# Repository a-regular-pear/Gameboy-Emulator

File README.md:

# Gameboy Emulator

A Gameboy emulator for the Teensy 4.1 microcontroller and PC (Windows and Linux).

## Features

* Nearly complete LR35902 (Gameboy CPU) implementation.
* Support for Memory Bank Controllers: MBC0, MBC1, MBC3, and MBC5.
* Native support for Teensy 4.1, Windows, and Linux.
* Runs on the Teensy 4.1 using internal memory (does not require external PSRAM to work).
* APU supports Channel 1 and Channel 2 on PC

## TODO

* Add audio (APU) support.
* Make the PPU (Picture Processing Unit) modes dynamic.
* Add support for the remaining memory banks (e.g., MBC2).
* Design a custom PCB for the Teensy 4.1 hardware setup.

## Software Needed

### For Teensy 4.1

* [PlatformIO](https://platformio.org/)
* [ILI9341_t3n](https://github.com/KurtE/ILI9341_t3n) (Hardware-optimized display library)

### For PC

* A C++17 compatible compiler (GCC)
* [CMake](https://cmake.org/)
* [SDL2](https://www.libsdl.org/) and SDL2_ttf
* For Windows: [MSYS2](https://www.msys2.org/) (UCRT64 environment)

## Build Instructions

### Teensy 4.1

Make sure the hardware pins for the buttons are connected as follows:

* **Right:** 0, **Left:** 1, **Up:** 2, **Down:** 3, **B:** 4, **A:** 5, **Select:** 6, **Start:** 7

Connect the ILI9341 display to the following SPI pins:

* **CS:** 10, **DC:** 9, **RST:** 8, **MOSI:** 11, **SCK:** 13, **MISO:** 12

To build:

1. Open the project in PlatformIO.
2. Make sure you are using the `teensy41` project environment.
3. Compile and upload to the board.
4. To add ROMs, format a MicroSD card (FAT32), load the `.gb` files onto the root directory, and insert it into the Teensy.

### Linux

Install `cmake`, `gcc`, `g++`, and the SDL2 development libraries using your distribution's package manager (e.g., `sudo apt install cmake gcc g++ libsdl2-dev libsdl2-ttf-dev` on Debian/Ubuntu).

Then, navigate to the project directory and run:

```bash
mkdir -p build
cd build
cmake ..
make
./emulator

```

To load ROMs, place the `.gb` files in the same directory as the executable.

### Windows (MSYS2)

**1. Install MSYS2**
Download the installer from [msys2.org](https://www.msys2.org/) and run it. Accept the default installation folder (usually `C:\msys64`). Once finished, open the **MSYS2 UCRT64** terminal (this is the recommended environment for modern Windows development).

**2. Update the System**
In the UCRT64 terminal, update the package database and core system packages:

```bash
pacman -Syu

```

**3. Install the Toolchain and Libraries**
Install the GCC compiler, CMake, standard Make tool, SDL2, and SDL2_ttf using the `pacman` package manager.

*(Note: We are explicitly installing `mingw-w64-ucrt-x86_64-make` instead of Ninja).*

```bash
pacman -S mingw-w64-ucrt-x86_64-gcc \
          mingw-w64-ucrt-x86_64-cmake \
          mingw-w64-ucrt-x86_64-make \
          mingw-w64-ucrt-x86_64-SDL2 \
          mingw-w64-ucrt-x86_64-SDL2_ttf

```

**4. Configure and Build**
Open the **MSYS2 UCRT64** terminal (or standard CMD/PowerShell if you have added MSYS2 to your PATH), navigate to your project folder using the `cd` command, and run the following commands:

**Generate the build files (using MinGW Makefiles):**

```bash
cmake -G "MinGW Makefiles" -B build

```

**Compile the executable:**

```bash
cmake --build build

```

**Run the compiled application:**

```bash
./build/emulator.exe

```

To load ROMs, place the `.gb` files in the directory where `./build/emulator.exe` is executed.

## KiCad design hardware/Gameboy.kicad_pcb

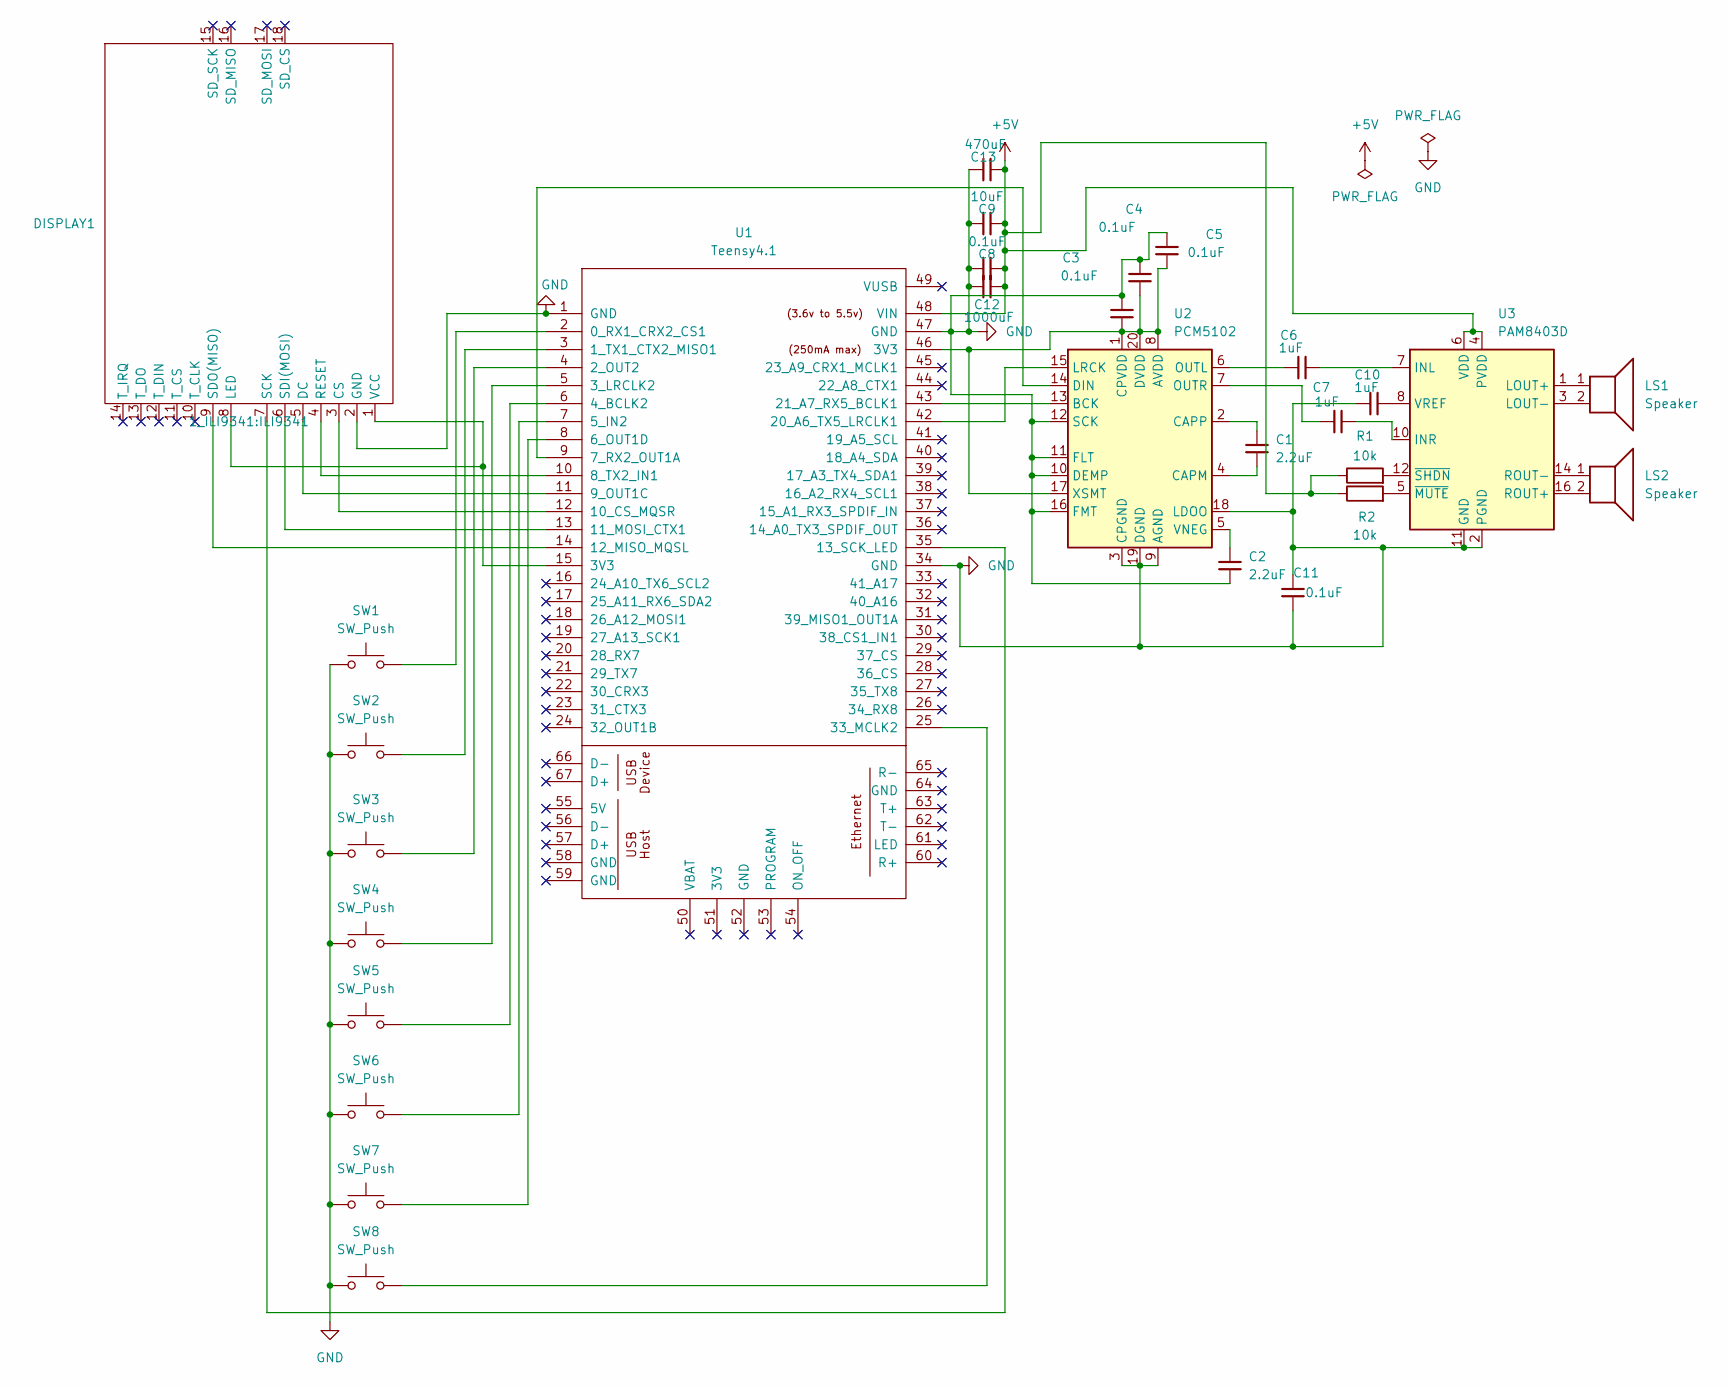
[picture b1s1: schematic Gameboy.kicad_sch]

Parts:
C1, C2: 2.2uF; C_0805_2012Metric_Pad1.18x1.45mm_HandSolder
C3, C4, C5, C8, C11: 0.1uF; C_0805_2012Metric_Pad1.18x1.45mm_HandSolder
C6, C7, C10: 1uF; C_0805_2012Metric_Pad1.18x1.45mm_HandSolder
C9: 10uF; C_0805_2012Metric_Pad1.18x1.45mm_HandSolder
C12: 1000uF; CP_Radial_D10.0mm_P5.00mm
C13: 470uF; CP_Radial_D8.0mm_P3.50mm
DISPLAY1: ILI9341
LS1, LS2: Speaker; JST_PH_B2B-PH-K_1x02_P2.00mm_Vertical
R1, R2: 10k; R_Axial_DIN0207_L6.3mm_D2.5mm_P10.16mm_Horizontal
SW1, SW2, SW3, SW4, SW5, SW6, SW7, SW8: SW_Push; Silicone button
U1: Teensy4.1; Teensy41
U2: PCM5102; TSSOP-20_4.4x6.5mm_P0.65mm
U3: PAM8403D; SOIC-16_3.9x9.9mm_P1.27mm

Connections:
+5V: C8.1, C9.1, C12.1, C13.1, R1.1, R2.1, U1.48 (VIN), U3.4 (PVDD), U3.6 (VDD), U3.13 (PVDD)
GND: C2.1, C3.2, C4.2, C5.2, C8.2, C9.2, C10.2, C11.1, C11.2, C12.2, C13.2, DISPLAY1.2 (GND), SW1.1, SW2.1, SW3.1, SW4.1, SW5.1, SW6.1, SW7.1, SW8.1, U1.1 (GND), U1.34 (GND), U1.47 (GND), U2.3 (CPGND), U2.9 (AGND), U2.10 (DEMP), U2.11 (FLT), U2.12 (SCK), U2.16 (FMT), U2.18 (LDOO), U2.19 (DGND), U3.2 (PGND), U3.11 (GND), U3.15 (PGND)
unnamed: DISPLAY1.3 (CS), U1.12 (10_CS_MQSR)
unnamed: DISPLAY1.5 (DC), U1.11 (9_OUT1C)
unnamed: DISPLAY1.1 (VCC), DISPLAY1.8 (LED), U1.15 (3V3)
unnamed: DISPLAY1.4 (RESET), U1.10 (8_TX2_IN1)
unnamed: DISPLAY1.7 (SCK), U1.35 (13_SCK_LED)
unnamed: DISPLAY1.6 (SDI(MOSI)), U1.13 (11_MOSI_CTX1)
unnamed: DISPLAY1.9 (SDO(MISO)), U1.14 (12_MISO_MQSL)
unnamed: SW1.2, U1.2 (0_RX1_CRX2_CS1)
unnamed: SW2.2, U1.3 (1_TX1_CTX2_MISO1)
unnamed: SW3.2, U1.4 (2_OUT2)
unnamed: SW4.2, U1.5 (3_LRCLK2)
unnamed: SW5.2, U1.6 (4_BCLK2)
unnamed: SW6.2, U1.7 (5_IN2)
unnamed: SW7.2, U1.8 (6_OUT1D)
unnamed: U1.9 (7_RX2_OUT1A), U2.14 (DIN)
unnamed: U1.42 (20_A6_TX5_LRCLK1), U2.15 (LRCK)
unnamed: U1.43 (21_A7_RX5_BCLK1), U2.13 (BCK)
unnamed: SW8.2, U1.25 (33_MCLK2)
unnamed: C3.1, C4.1, C5.1, U1.46 (3V3), U2.1 (CPVDD), U2.8 (AVDD), U2.17 (XSMT), U2.20 (DVDD)
unnamed: C1.1, U2.4 (CAPM)
unnamed: C1.2, U2.2 (CAPP)
unnamed: C6.2, U2.6 (OUTL)
unnamed: C7.2, U2.7 (OUTR)
unnamed: C2.2, U2.5 (VNEG)
unnamed: C6.1, U3.7 (INL)
unnamed: C7.1, U3.10 (INR)
unnamed: LS1.1, U3.1 (LOUT+)
unnamed: LS1.2, U3.3 (LOUT-)
unnamed: LS2.2, U3.16 (ROUT+)
unnamed: LS2.1, U3.14 (ROUT-)
unnamed: C10.1, U3.8 (VREF)
unnamed: R2.2, U3.5 (~MUTE)
unnamed: R1.2, U3.12 (~SHDN)

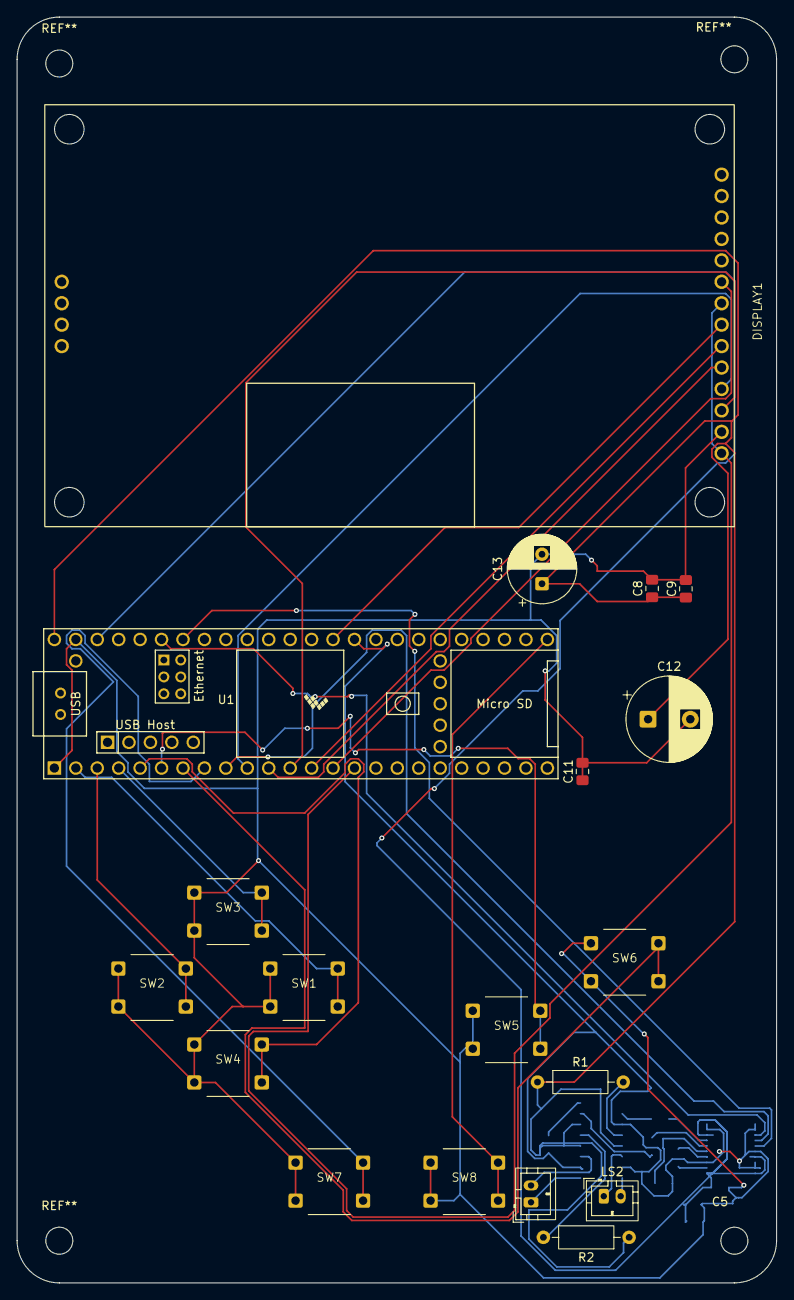
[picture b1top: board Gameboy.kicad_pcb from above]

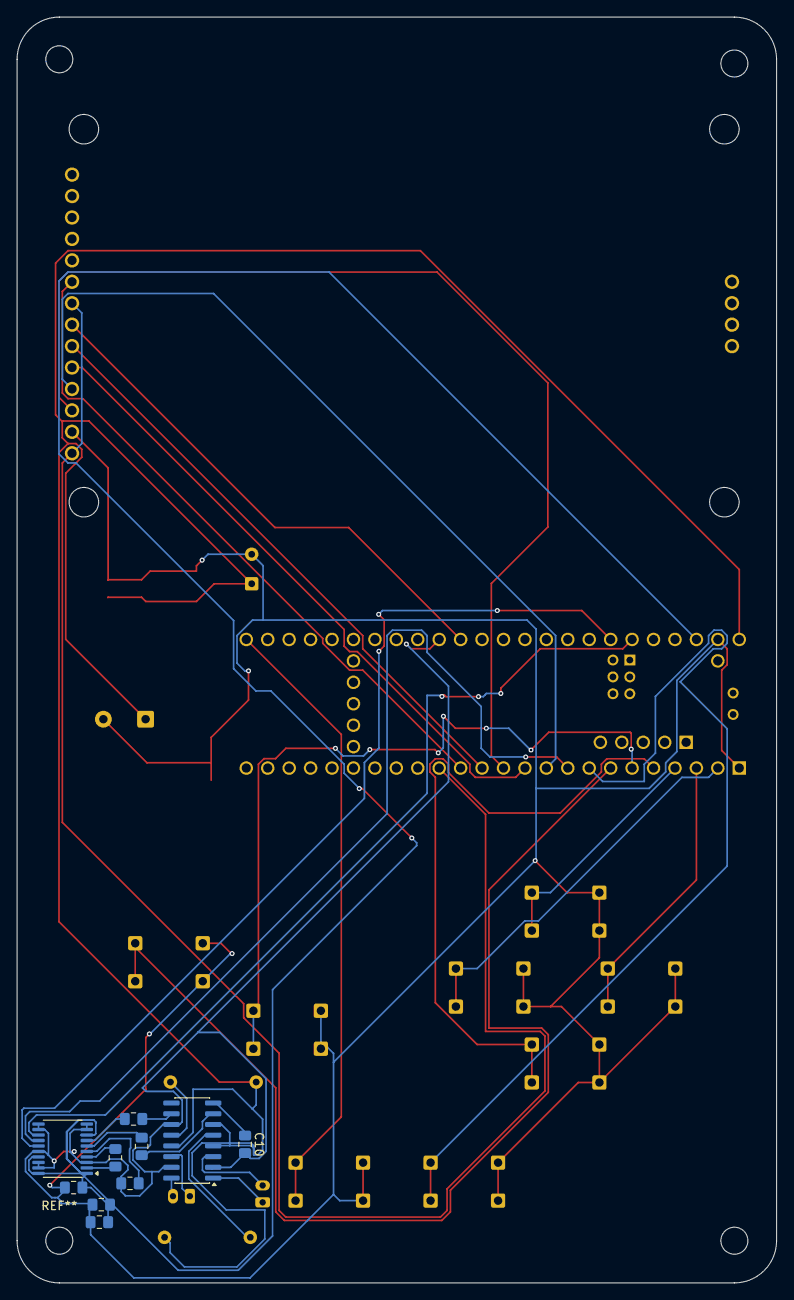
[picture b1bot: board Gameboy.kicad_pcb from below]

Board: 2 copper layers, 90.0 x 150.0 mm, 29 parts (10 on the bottom side), 35 nets.

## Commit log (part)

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2026-03-01 implement registers
2026-03-01 add Block 1 and 2 of CPU ISA
2026-03-01 fix halt bug in block 1
2026-03-02 add Block 3 of CPU ISA
2026-03-05 add Block 0 of CPU ISA
2026-03-05 complete CPU ISA and verify with Blargg tests 03-11
2026-03-06 Create basic ram structure
2026-03-08 Add basic ram functionality, NO MBC only
2026-03-08 Implement basic way to test Blargg's test roms
2026-03-08 Implement interrupt handling
2026-03-08 Add halt
2026-03-08 Add stop
2026-03-08 Fix bugs
2026-03-11 Add timer to the bus
2026-03-11 CPU returns cycles
2026-03-13 Implement timer functionality
2026-03-15 Add MBC1 support
2026-03-16 Implement registers, stat interrupt and basic timing on the ppu
2026-03-19 Add background rendering, and basic display implemantation
2026-03-21 Make display pillbox
2026-03-21 Add sprite rendering
2026-03-21 Preserve interrupt enables on stat when ppu is off
2026-03-22 Improve timing
2026-03-22 Add window
2026-03-22 Add input
2026-03-23 Change input to pullup
2026-03-23 Include the option of streaming from sd when ROM is too large
2026-03-24 Add mbc5 support
2026-03-25 Add MBC3 support
2026-03-25 Add saving
2026-03-25 Remove Arduino header from Cartridge
2026-03-25 Add way to load roms
